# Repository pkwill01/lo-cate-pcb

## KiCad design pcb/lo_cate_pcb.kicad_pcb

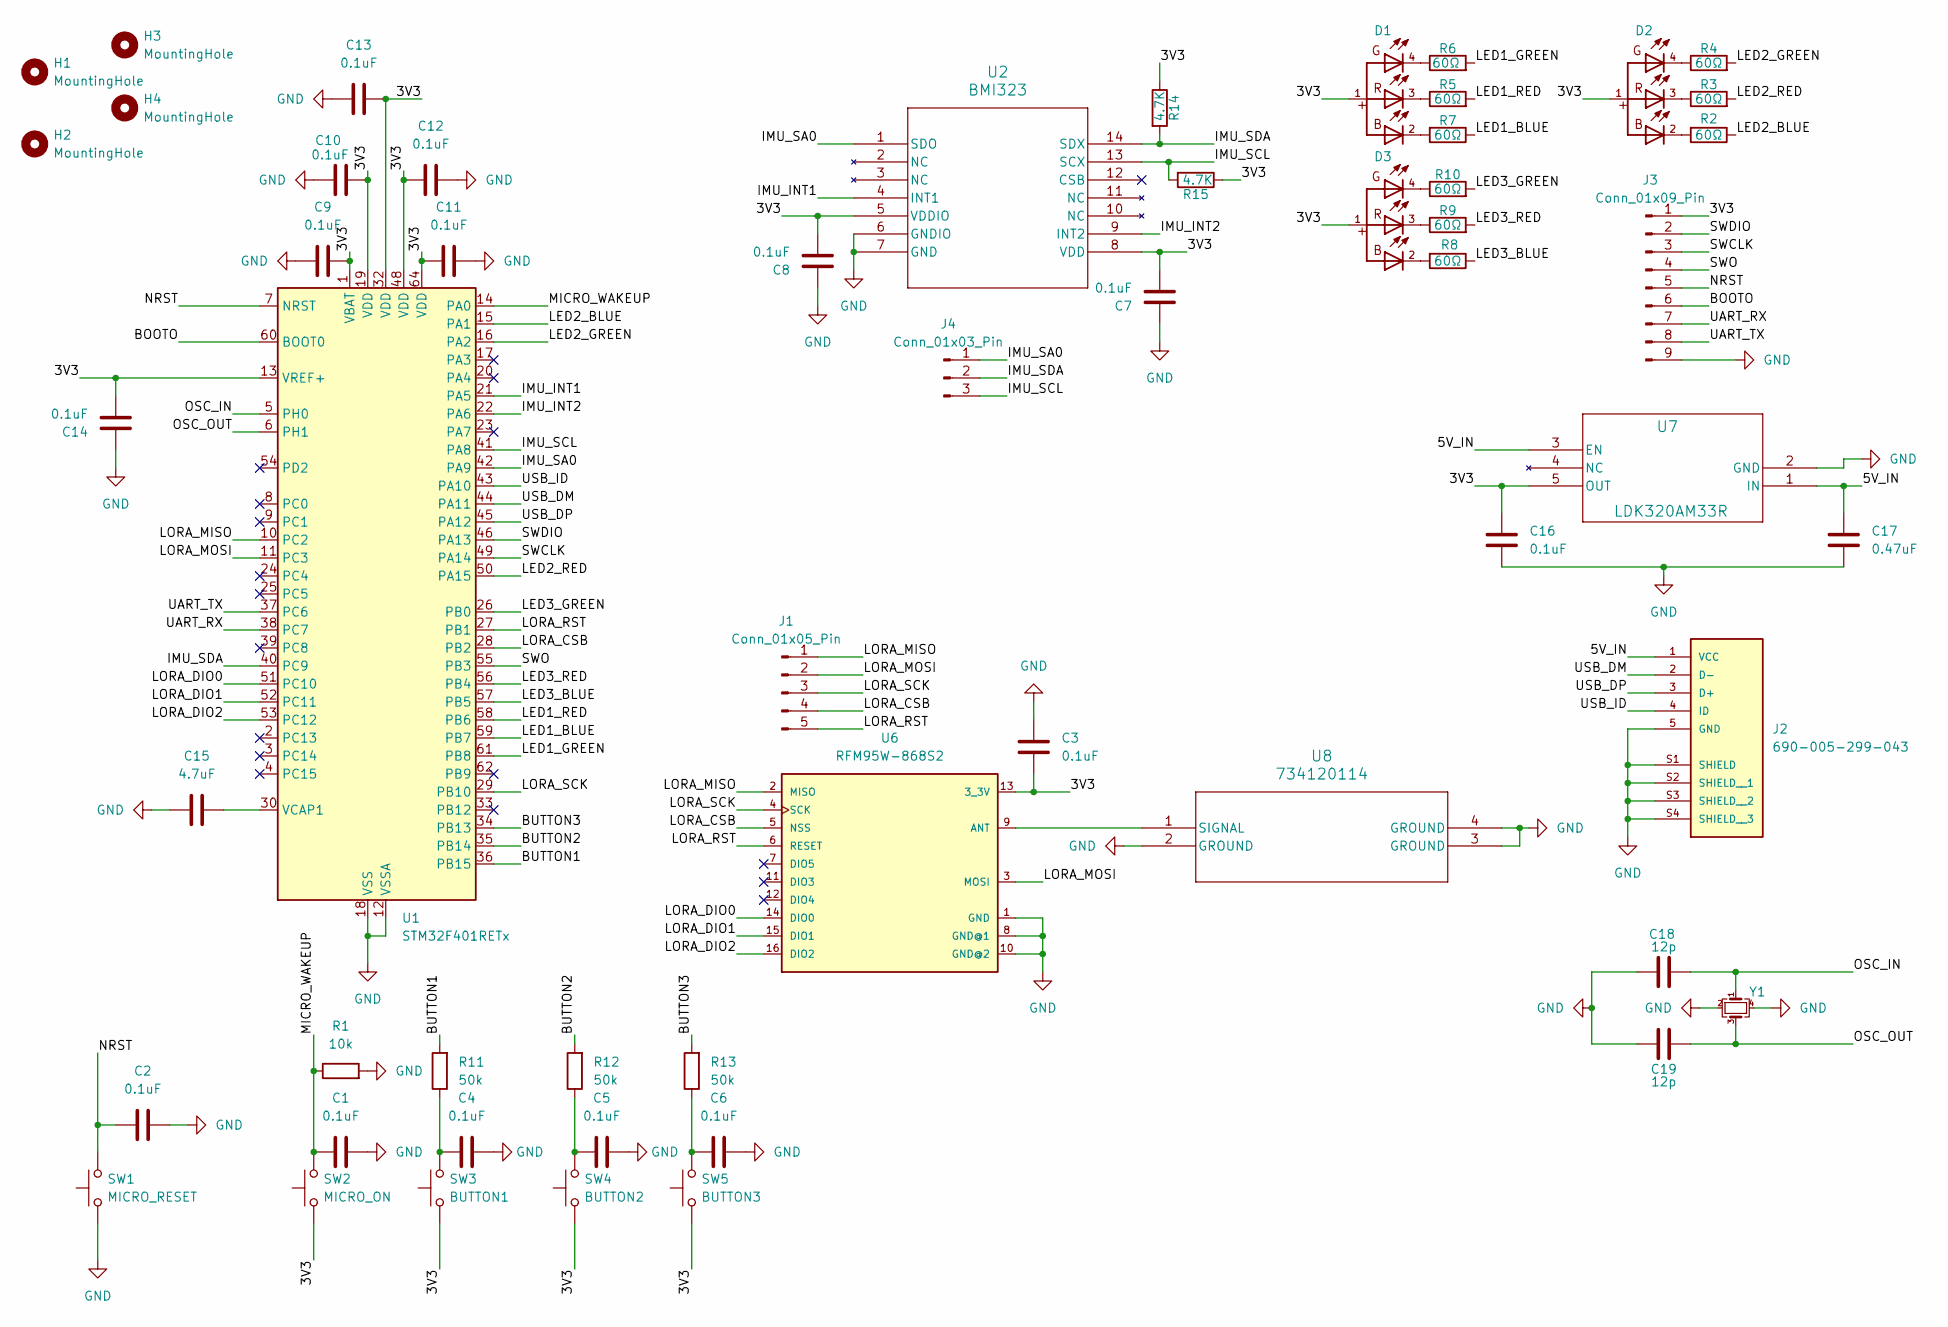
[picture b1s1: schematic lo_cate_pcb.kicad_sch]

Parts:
C1, C2, C3, C4, C5, C6, C7, C8, C9, C10, C11, C12, C13, C14, C16: 0.1uF; C_0805_2012Metric_Pad1.18x1.45mm_HandSolder
C15: 4.7uF; C_0805_2012Metric_Pad1.18x1.45mm_HandSolder
C17: 0.47uF; C_0805_2012Metric_Pad1.18x1.45mm_HandSolder
C18, C19: 12p; C_0805_2012Metric_Pad1.18x1.45mm_HandSolder
D1, D2, D3: WL-SFTW_3528_PLCC4
H1, H2, H3, H4: MountingHole; MountingHole_3.2mm_M3
J1: Conn_01x05_Pin; PinSocket_1x05_P2.54mm_Vertical
J2: 690-005-299-043; EDAC_690-005-299-043; PARTREV 11
J3: Conn_01x09_Pin; PinSocket_1x09_P2.54mm_Vertical
J4: Conn_01x03_Pin; PinSocket_1x03_P2.54mm_Vertical
R1: 10k; R_0805_2012Metric_Pad1.20x1.40mm_HandSolder
R2, R3, R4, R5, R6, R7, R8, R9, R10: 60Ω; R_0805_2012Metric_Pad1.20x1.40mm_HandSolder
R11, R12, R13: 50k; R_0805_2012Metric_Pad1.20x1.40mm_HandSolder
R14, R15: 4.7K; R_0805_2012Metric_Pad1.20x1.40mm_HandSolder
SW1: MICRO_RESET; SW_SPST_PTS647_Sx38
SW2: MICRO_ON; SW_SPST_PTS647_Sx38
SW3: BUTTON1; SW_SPST_PTS647_Sx38
SW4: BUTTON2; SW_SPST_PTS647_Sx38
SW5: BUTTON3; SW_SPST_PTS647_Sx38
U1: STM32F401RETx; LQFP-64_10x10mm_P0.5mm
U2: BMI323; BMI323_BOS-M
U6: RFM95W-868S2; XCVR_RFM95W-868S2
U7: LDK320AM33R; SOT23-5L_STM-M
U8: 734120114; 73412-0114_MOL
Y1: Crystal_GND24_Small; Crystal_SMD_7050-4Pin_7.0x5.0mm

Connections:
/3V3: C3.2, C7.2, C8.2, C9.1, C10.1, C11.2, C12.2, C13.2, C14.2, C16.1, D1.1, D2.1, D3.1, J3.1, R14.1, R15.1, SW2.1, SW3.1, SW4.1, SW5.1, U1.1 (VBAT), U1.13 (VREF+), U1.19 (VDD), U1.32 (VDD), U1.48 (VDD), U1.64 (VDD), U2.5 (VDDIO), U2.8 (VDD), U6.13 (3_3V), U7.5 (OUT)
/5V_IN: C17.1, J2.1 (VCC), U7.1 (IN), U7.3 (EN)
/BOOTO: J3.6, U1.60 (BOOT0)
/BUTTON1: R11.2, U1.36 (PB15)
/BUTTON2: R12.2, U1.35 (PB14)
/BUTTON3: R13.2, U1.34 (PB13)
/IMU_INT1: U1.21 (PA5), U2.4 (INT1)
/IMU_INT2: U1.22 (PA6), U2.9 (INT2)
/IMU_SA0: J4.1, U1.42 (PA9), U2.1 (SDO)
/IMU_SCL: J4.3, R15.2, U1.41 (PA8), U2.13 (SCX)
/IMU_SDA: J4.2, R14.2, U1.40 (PC9), U2.14 (SDX)
/LED1_BLUE: R7.1, U1.59 (PB7)
/LED1_GREEN: R6.2, U1.61 (PB8)
/LED1_RED: R5.2, U1.58 (PB6)
/LED2_BLUE: R2.1, U1.15 (PA1)
/LED2_GREEN: R4.2, U1.16 (PA2)
/LED2_RED: R3.2, U1.50 (PA15)
/LED3_BLUE: R8.1, U1.57 (PB5)
/LED3_GREEN: R10.2, U1.26 (PB0)
/LED3_RED: R9.2, U1.56 (PB4)
/LORA_CSB: J1.4, U1.28 (PB2), U6.5 (NSS)
/LORA_DIO0: U1.51 (PC10), U6.14 (DIO0)
/LORA_DIO1: U1.52 (PC11), U6.15 (DIO1)
/LORA_DIO2: U1.53 (PC12), U6.16 (DIO2)
/LORA_MISO: J1.1, U1.10 (PC2), U6.2 (MISO)
/LORA_MOSI: J1.2, U1.11 (PC3), U6.3 (MOSI)
/LORA_RST: J1.5, U1.27 (PB1), U6.6 (RESET)
/LORA_SCK: J1.3, U1.29 (PB10), U6.4 (SCK)
/MICRO_WAKEUP: C1.2, R1.1, SW2.2, U1.14 (PA0)
/NRST: C2.2, J3.5, SW1.2, U1.7 (NRST)
/OSC_IN: C18.1, U1.5 (PH0), Y1.1
/OSC_OUT: C19.1, U1.6 (PH1), Y1.3
/SWCLK: J3.3, U1.49 (PA14)
/SWDIO: J3.2, U1.46 (PA13)
/SWO: J3.4, U1.55 (PB3)
/UART_RX: J3.7, U1.38 (PC7)
/UART_TX: J3.8, U1.37 (PC6)
/USB_DM: J2.2 (D-), U1.44 (PA11)
/USB_DP: J2.3 (D+), U1.45 (PA12)
/USB_ID: J2.4 (ID), U1.43 (PA10)
GND: C1.1, C2.1, C3.1, C4.1, C5.1, C6.1, C7.1, C8.1, C9.2, C10.2, C11.1, C12.1, C13.1, C14.1, C15.2, C16.2, C17.2, C18.2, C19.2, J2.5 (GND), J2.S1 (SHIELD), J2.S2 (SHIELD__1), J2.S3 (SHIELD__2), J2.S4 (SHIELD__3), J3.9, R1.2, SW1.1, U1.12 (VSSA), U1.18 (VSS), U1.31 (VSS), U1.47 (VSS), U1.63 (VSS), U2.6 (GNDIO), U2.7 (GND), U6.1 (GND), U6.8 (GND@1), U6.10 (GND@2), U7.2 (GND), U8.2 (GROUND), U8.3 (GROUND), U8.4 (GROUND), Y1.2, Y1.4
unnamed: C4.2, R11.1, SW3.2
unnamed: C5.2, R12.1, SW4.2
unnamed: C6.2, R13.1, SW5.2
unnamed: D1.2, R7.2
unnamed: D1.3, R5.1
unnamed: D1.4, R6.1
unnamed: D2.2, R2.2
unnamed: D2.3, R3.1
unnamed: D2.4, R4.1
unnamed: D3.2, R8.2
unnamed: D3.3, R9.1
unnamed: D3.4, R10.1
unnamed: C15.1, U1.30 (VCAP1)
unnamed: U6.9 (ANT), U8.1 (SIGNAL)

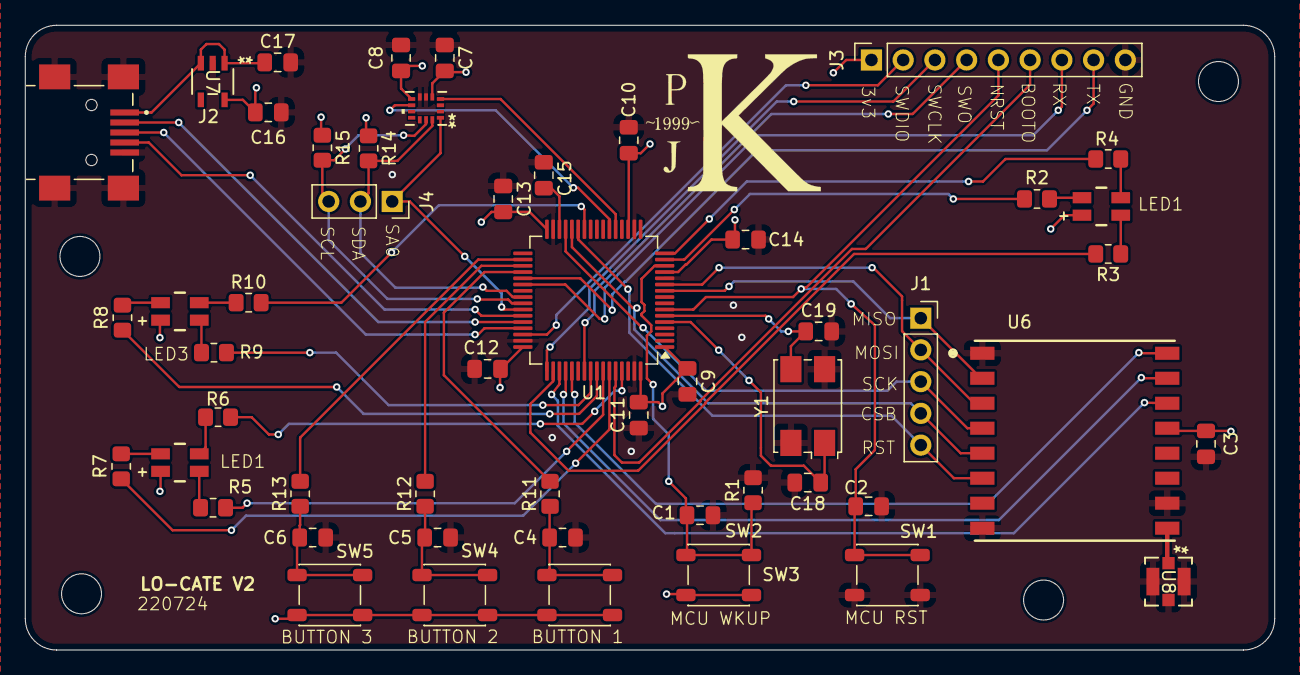
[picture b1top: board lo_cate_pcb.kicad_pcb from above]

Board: 4 copper layers, 100.0 x 50.0 mm, 56 parts (0 on the bottom side), 55 nets.

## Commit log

2024-07-20 Added the PCB files into the repo
2024-07-22 Made changes the PCB to take it to version 2, bom just needs updating now
2024-07-23 BOM Updated
